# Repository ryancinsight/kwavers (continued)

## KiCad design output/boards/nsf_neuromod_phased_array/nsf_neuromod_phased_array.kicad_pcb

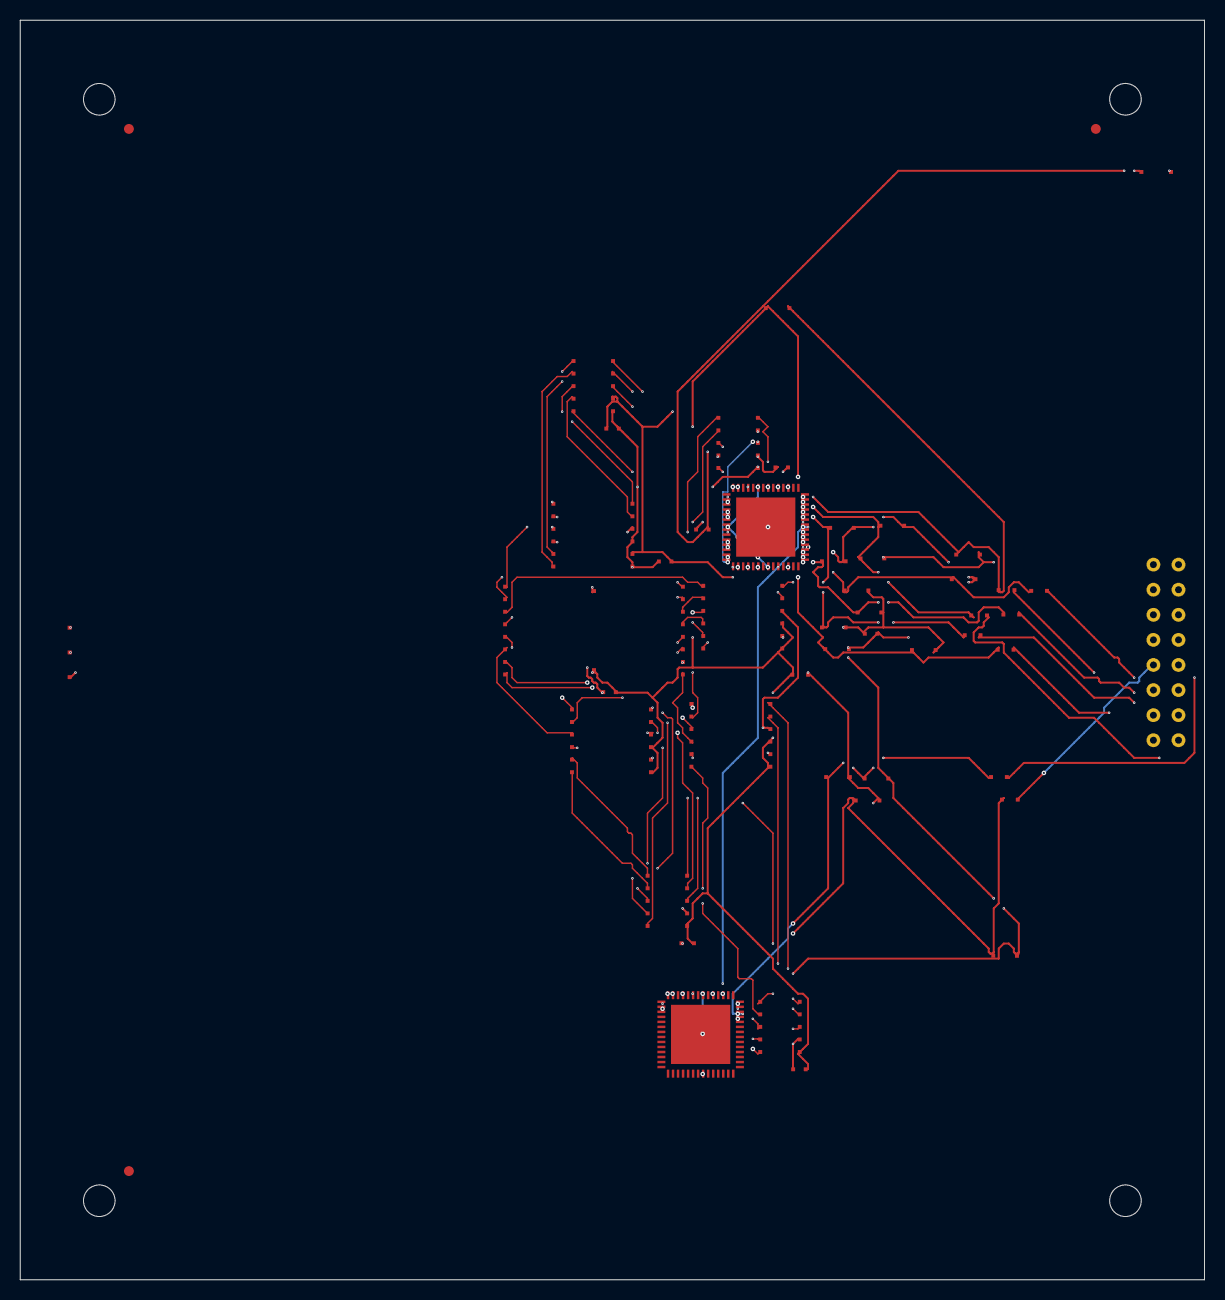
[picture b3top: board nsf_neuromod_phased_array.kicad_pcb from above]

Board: 6 copper layers, 119.9 x 127.5 mm, 54 parts (0 on the bottom side), 69 nets.

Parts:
C1, C2, C3, C4, C100, C101, C102, C103: CL10B104KB8NNNC
D1, D2, D3, D4, D5, D6, D7, D8, D9, D10, D11, D12, D13, D14, D15, D16: STPS2200
FB1: BLM18PG471SN1
FID: FIDUCIAL
FID#2, FID#3: FIDUCIAL
J1: CON16_2X8_TU_TSW_SAI
J2: J_HV_IN
J3: J_LV_IN
MH: MountingHole
MH#2, MH#3, MH#4: MountingHole
Q1, Q2: TC8020K6-G
R1, R2, R3, R4, R5, R6, R7, R8: RC0805FR-0756RL
U1: XC7A200T-2FBG484I
U2, U3, U4, U5: ADUM3480
U10, U11, U12, U13: MD1822K6-G

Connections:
CTRL_HS_0: U1.1, U2.1
CTRL_HS_1: U1.2, U2.3
CTRL_HS_2: U1.3, U3.1
CTRL_HS_3: U1.4, U3.3
CTRL_HS_4: U1.5, U4.1
CTRL_HS_5: U1.6, U4.3
CTRL_HS_6: U1.7, U5.1
CTRL_HS_7: U1.8, U5.3
CTRL_LS_0: U1.9, U2.2
CTRL_LS_1: U1.10, U2.4
CTRL_LS_2: U1.11, U3.2
CTRL_LS_3: U1.12, U3.4
CTRL_LS_4: U1.13, U4.2
CTRL_LS_5: U1.14, U4.4
CTRL_LS_6: U1.15, U5.2
CTRL_LS_7: U1.16, U5.4
DGND: C3.2, C4.2, C100.2, C101.2, C102.2, C103.2, FB1.1, J3.3, U1.18, U2.10, U2.12, U3.10, U3.12, U4.10, U4.12, U5.10, U5.12, U10.10, U11.10, U12.10, U13.10
ELEM_0: J1.1, R1.2
ELEM_1: J1.2, R2.2
ELEM_2: J1.3, R3.2
ELEM_3: J1.4, R4.2
ELEM_4: J1.5, R5.2
ELEM_5: J1.6, R6.2
ELEM_6: J1.7, R7.2
ELEM_7: J1.8, R8.2
GIN_HS_0: U2.5, U10.1
GIN_HS_1: U2.7, U10.3
GIN_HS_2: U3.5, U11.1
GIN_HS_3: U3.7, U11.3
GIN_HS_4: U4.5, U12.1
GIN_HS_5: U4.7, U12.3
GIN_HS_6: U5.5, U13.1
GIN_HS_7: U5.7, U13.3
GIN_LS_0: U2.6, U10.2
GIN_LS_1: U2.8, U10.4
GIN_LS_2: U3.6, U11.2
GIN_LS_3: U3.8, U11.4
GIN_LS_4: U4.6, U12.2
GIN_LS_5: U4.8, U12.4
GIN_LS_6: U5.6, U13.2
GIN_LS_7: U5.8, U13.4
NG_0: Q1.1, U10.6
NG_1: Q1.2, U10.8
NG_2: Q1.4, U11.6
NG_3: Q1.14, U11.8
NG_4: Q1.13, U12.6
NG_5: Q1.11, U12.8
NG_6: Q2.1, U13.6
NG_7: Q2.2, U13.8
PGND: C1.2, C2.2, D2.1, D4.1, D6.1, D8.1, D10.1, D12.1, D14.1, D16.1, FB1.2, J1.9, J1.10, J1.11, J1.12, J1.13, J1.14, J1.15, J1.16, J2.2, Q1.7, Q1.8, Q1.18, Q1.20, Q1.22, Q1.49, Q1.51, Q1.53, Q1.57, Q2.22, Q2.49, Q2.51, Q2.53, Q2.57
PG_0: Q1.55, U10.5
PG_1: Q1.56, U10.7
PG_2: Q1.5, U11.5
PG_3: Q1.16, U11.7
PG_4: Q1.15, U12.5
PG_5: Q1.10, U12.7
PG_6: Q2.55, U13.5
PG_7: Q2.56, U13.7
TXO_0: D1.1, D2.2, Q1.41, Q1.42, R1.1
TXO_1: D3.1, D4.2, Q1.39, Q1.40, R2.1
TXO_2: D5.1, D6.2, Q1.37, Q1.38, R3.1
TXO_3: D7.1, D8.2, Q1.29, Q1.30, R4.1
TXO_4: D9.1, D10.2, Q1.31, Q1.32, R5.1
TXO_5: D11.1, D12.2, Q1.33, Q1.34, R6.1
TXO_6: D13.1, D14.2, Q2.41, Q2.42, R7.1
TXO_7: D15.1, D16.2, Q2.39, Q2.40, R8.1
VDDH: C1.1, C2.1, D1.2, D3.2, D5.2, D7.2, D9.2, D11.2, D13.2, D15.2, J2.1, Q1.24, Q1.26, Q1.35, Q1.36, Q1.45, Q1.47, Q2.45, Q2.47
VDD_3V3: C4.1, J3.1, U1.17, U2.9, U3.9, U4.9, U5.9
VDD_5V: C3.1, C100.1, C101.1, C102.1, C103.1, J3.2, U2.11, U3.11, U4.11, U5.11, U10.9, U11.9, U12.9, U13.9
